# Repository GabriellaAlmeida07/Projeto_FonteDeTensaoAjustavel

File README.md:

# Projeto_FonteDeTensaoAjustável
## Descrição:
Projeto da disciplina SSC0180 - Eletrônica para Computação, ministrada pelo professor Eduardo do Valle Simoes, com o objetivo de projetar uma
fonte reficadora capaz de transformar corrente alternada de tensão, em corrente contínua, com valor de tensão ajustável entre 3 e 12 volts.

## Componentes:

| Componente             |  Quantidade   | Especificações    | Valor Unitário |
|:----------------------:|:-------------:|:-----------------:|:--------------:|
| Diodo Retificador      | 5             | 1N4007 LGE=1N4004 | R$ 0,20        |
| Capacitor              | 1             | 680UFX25V         | R$ 5,80        |
| LED                    | 2             | 5mm VM difuso     | R$ 0,50        |
| Resistor               | 5             | CR25 3K3          | R$ 0,07        |
| Resistor               | 5             | CR25 1K           | R$ 0,07        |
| Resistor               | 5             | CR25 4K7          | R$ 0,07        |
| Resistor               | 5             | CR25 120R         | R$ 0,07        |
| Resistor               | 5             | CR25 680R         | R$ 0,07        |
| Diodo Zener            | 2             | 13V 1W - 1N4743   | R$ 0,50        |
| Potenciômetro          | 2             | 1W B10K B-16      | R$ 7,00        |
| Transistor             | 1             | BC368 N-25V-1A-0  | R$ 0.44        |
| Jumper Macho           | 10            | 20cm              | R$ 0,70        |
| Fusível                | 2             | 20 AG 0.1A        | R$ 1,10        |
| Varistor               | 1             | 150VAC 7D 241K    | R$ 1,50        |
|**Total**               |               |                   | **R$ 35,69**   |

## Sobre os componentes
#### Transformador:
A fonte de corrente alternada (tomada) fornece uma ddp de 127V, por isso é necessário o uso do transformador que é capaz de baixar a tensão de 110 volts para 12 volts.

#### Fusível:
O fusível é usado com o intuito de "proteger" o circuito de correntes elétricas excessivas, visto que se houver sobrecarga, ele irá interromper o circuito.

#### Ponte de diodos:
Formada por quatro diodos retificadores, é responsável por permitir que uma corrente alternada seja convertida em corrente contínua.

#### Varistor:
Também usado para maior segurança ao circuito, pois quando uma tensão excessiva é aplicada ao varistor, sua resistência diminui rapidamente, permitindo que ele conduza a corrente elétrica e desvie a energia extra para a terra ou para a fonte de alimentação.

#### Capacitor:
Responsável por controlar a ondulação da tensão no circuito, durante a alternância dos ciclos de corrente elétrica, o capacitor armazena energia (quando a tensão está alta) e libera quando a tensão cai.

#### Resistor:
O resistor limita o fluxo de corrente elétrica em um circuito, impedindo que a corrente ultrapasse o limite estabelecido por cada componente.

#### Diodo Zener:
Se comporta como um diodo normal, porém quando a tensão excede a tensão Zener, ele deixará "passar" somente a tensão limite, que no caso será 12V.

#### Transistor:
O transistor tem capacidade de controle da intensidade da corrente elétrica que passa por ele, sendo capaz de limitá-la, amplificá-la ou, até mesmo, atenuá-la.

#### Potenciômetro:
É um tipo de resistor que permite controlar a tensão entre 3 a 12V, no nosso caso.

## Fotos do circuito na protoboard

## Circuito Falstad
[Circuito Falstad](https://tinyurl.com/2gfmwb9f)

## Projeto do Esquemático EAGLE

## Projeto PCB EAGLE

## Cálculos
Queremos um Ripple pequeno (10%), e por isso é possível utilizar a fórmula simplificada C = i / (f * v) * ripple.

Seguindo o simulador Falstad, encontramos a tensão após a ponte de diodos de aproximadamente 18.18V e a corrente depois do capacitor de aproximadamente 120mA.

Sabemos que a fonte possui uma corrente alternada de 60Hz, daí obtemos f a partir de 2 * 60 = 120Hz, então basta aplicar a fórmula sobre os valores encontrados.

O resultado desta operação foi de 550uF, porém preferimos comprar um capacitor de 680uF (o segundo valor comercial mais próximo), por segurança.

## Vídeo do projeto

## Colaboradoes:
Gabriella Almeida - 15528121

Samuel Sandoval Bonachela - 13686282

Joao Victor De Bortoli Prado - 13672071

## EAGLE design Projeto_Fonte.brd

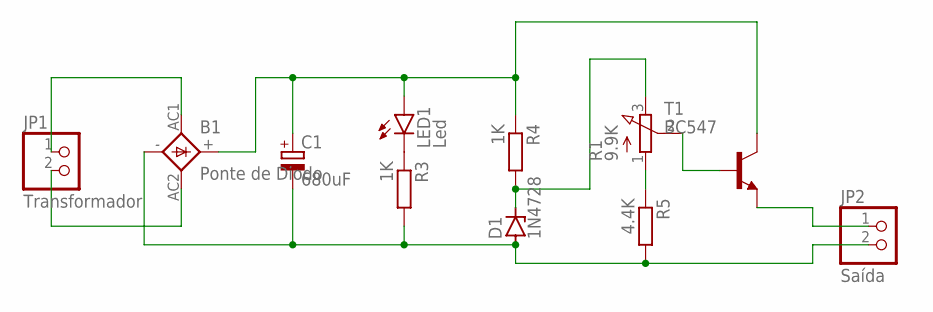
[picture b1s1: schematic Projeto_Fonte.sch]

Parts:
B1: Ponte de Diodo; 1KAB
C1: 680uF; E5-10,5
D1: 1N4728; DO41Z10
JP1: Transformador; 1X02
JP2: Saída; 1X02
LED1: Led; LED5MM
R1: 9.9K; 3RP/1610N
R3, R4: 1K; 0204/7
R5: 4.4K; 0204/7
T1: BC547; TO92

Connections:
unnamed: B1.AC1, JP1.1
unnamed: B1.AC2, JP1.2
unnamed: B1.+, C1.+, LED1.A, R4.1, T1.3 (C)
unnamed: B1.-, C1.-, D1.A, JP2.2, R3.2, R5.2
unnamed: LED1.K (C), R3.1
unnamed: D1.C, R1.3 (E), R4.2
unnamed: R1.1 (A), R5.1
unnamed: R1.2 (S), T1.2 (B)
unnamed: JP2.1, T1.1 (E)

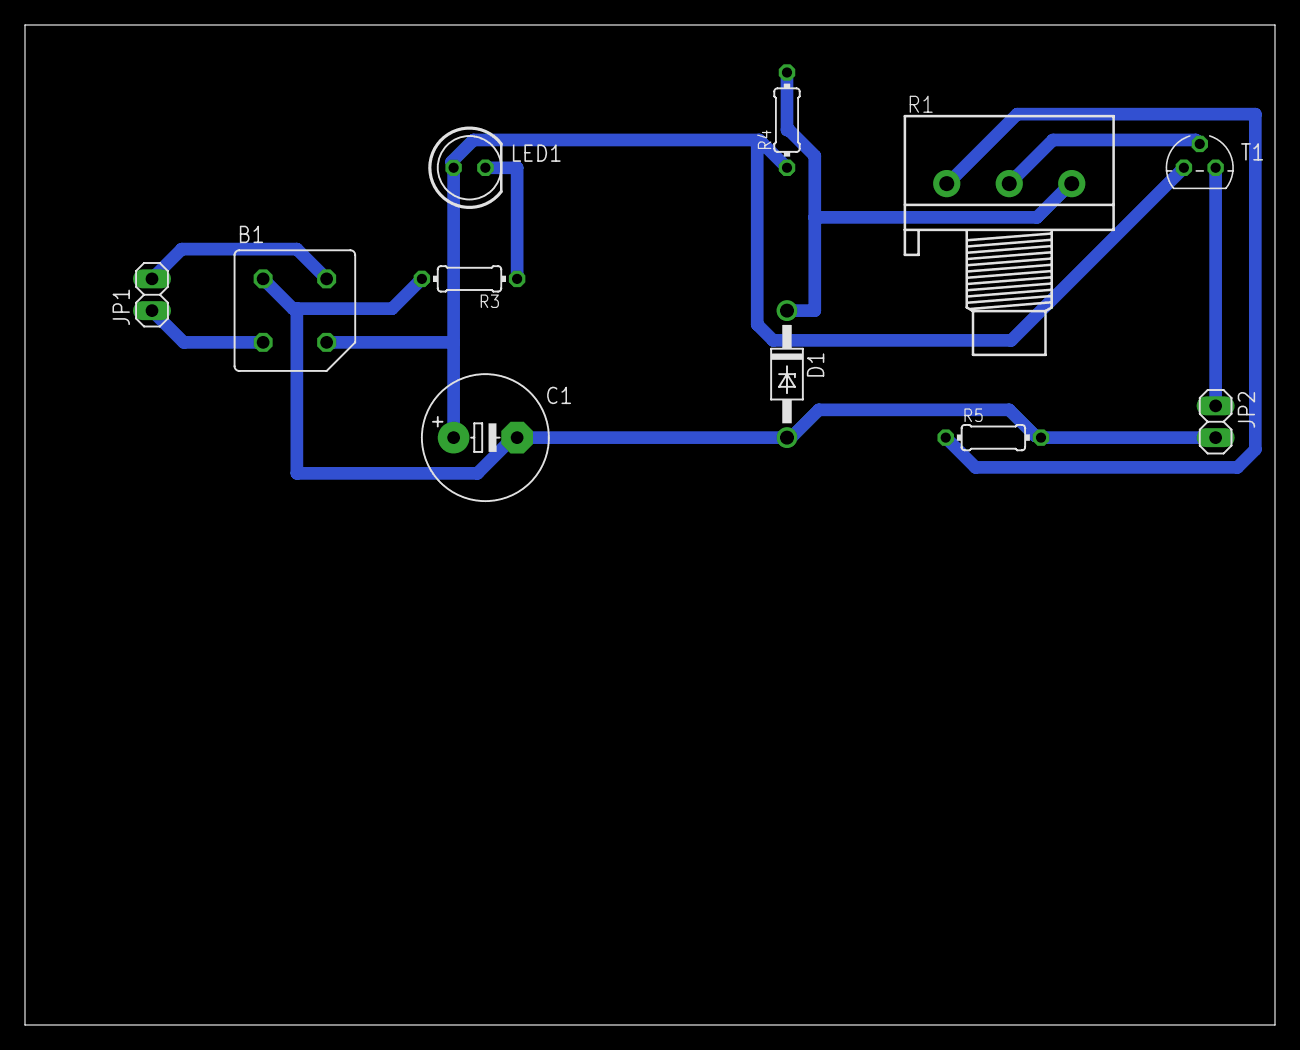
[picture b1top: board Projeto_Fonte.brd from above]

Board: 2 copper layers, 100.0 x 80.0 mm, 11 parts (0 on the bottom side), 9 nets.
